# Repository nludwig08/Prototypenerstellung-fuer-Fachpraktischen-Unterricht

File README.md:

# Prototypenerstellung für den Fachpraktischen Unterricht

Fünf elektronische Projekte für Schnupperschüler an der HTL Steyr.

| Nr. | Projekt | Beschreibung |
|-----|---------|--------------|
| 01 | [Elektronischer Würfel](01-elektronischer-wuerfel/) | ... |
| 02 | [Hau den Lukas](02-hau-den-lukas/) | ... |
| 03 | [Merkspiel](03-merkspiel/) | ... |
| 04 | [Zeitrate-Spiel](04-zeitrate-spiel/) | ... |
| 05 | [Wecker](05-wecker/) | ... |

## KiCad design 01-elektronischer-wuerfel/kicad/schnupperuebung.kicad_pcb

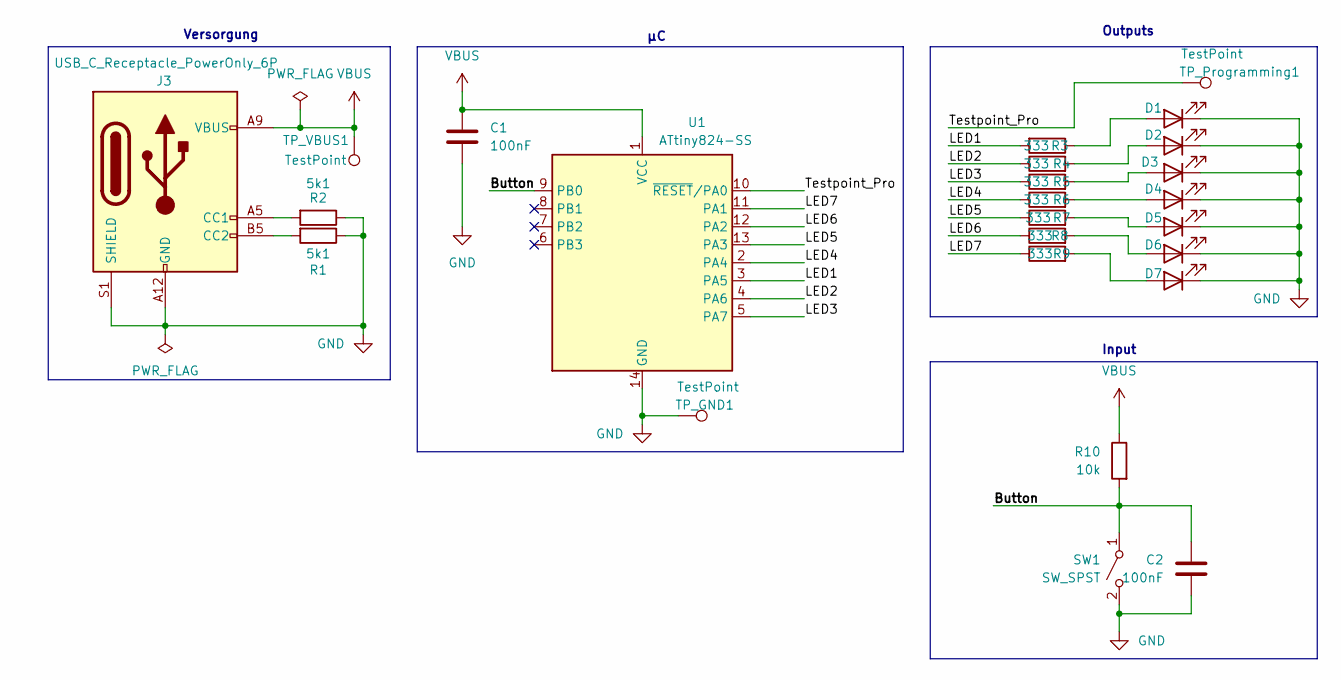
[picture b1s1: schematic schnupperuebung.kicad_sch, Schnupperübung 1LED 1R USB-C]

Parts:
C1, C2: 100nF; C_Disc_D5.0mm_W2.5mm_P5.00mm
D1, D2, D3, D4, D5, D6, D7: LED; LED_D5.0mm
J3: USB_C_Receptacle_PowerOnly_6P; USB_C_Receptacle_GCT_USB4125-xx-x-0190_6P_TopMnt_Horizontal
R1, R2: 5k1; R_0805_2012Metric_Pad1.20x1.40mm_HandSolder
R3, R4, R5, R6, R7, R8, R9: 333; R_Axial_DIN0207_L6.3mm_D2.5mm_P10.16mm_Horizontal
R10: 10k; R_Axial_DIN0207_L6.3mm_D2.5mm_P10.16mm_Horizontal
SW1: SW_SPST; C_Radial_D5.0mm_H5.0mm_P2.00mm
TP_GND1: TestPoint; TestPoint_Pad_D4.0mm
TP_Programming1: TestPoint; TestPoint_Pad_D4.0mm
TP_VBUS1: TestPoint; TestPoint_Pad_D4.0mm
U1: ATtiny824-SS; SOIC-14_3.9x8.7mm_P1.27mm

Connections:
/Button: C2.2, R10.2, SW1.1 (A), U1.9 (PB0)
/LED1: R3.2, U1.3 (PA5)
/LED2: R4.1, U1.4 (PA6)
/LED3: R5.1, U1.5 (PA7)
/LED4: R6.1, U1.2 (PA4)
/LED5: R7.1, U1.13 (PA3)
/LED6: R8.1, U1.12 (PA2)
/LED7: R9.1, U1.11 (PA1)
/Testpoint_Pro: TP_Programming1.1 (1_1), U1.10 (~RESET/PA0)
GND: C1.1, C2.1, D1.1 (K), D2.1 (K), D3.1 (K), D4.1 (K), D5.1 (K), D6.1 (K), D7.1 (K), J3.A12 (GND), J3.B12 (GND), J3.S1 (SHIELD), R1.1, R2.1, SW1.2 (B), TP_GND1.1 (1_1), U1.14 (GND)
unnamed: D1.2 (A), R3.1
unnamed: D2.2 (A), R4.2
unnamed: D3.2 (A), R5.2
unnamed: D4.2 (A), R6.2
unnamed: D5.2 (A), R7.2
unnamed: D6.2 (A), R8.2
unnamed: D7.2 (A), R9.2
unnamed: J3.A5 (CC1), R2.2
unnamed: J3.B5 (CC2), R1.2
VBUS: C1.2, J3.A9 (VBUS), J3.B9 (VBUS), R10.1, TP_VBUS1.1 (1_1), U1.1 (VCC)

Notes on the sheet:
Outputs
Input
Versorgung

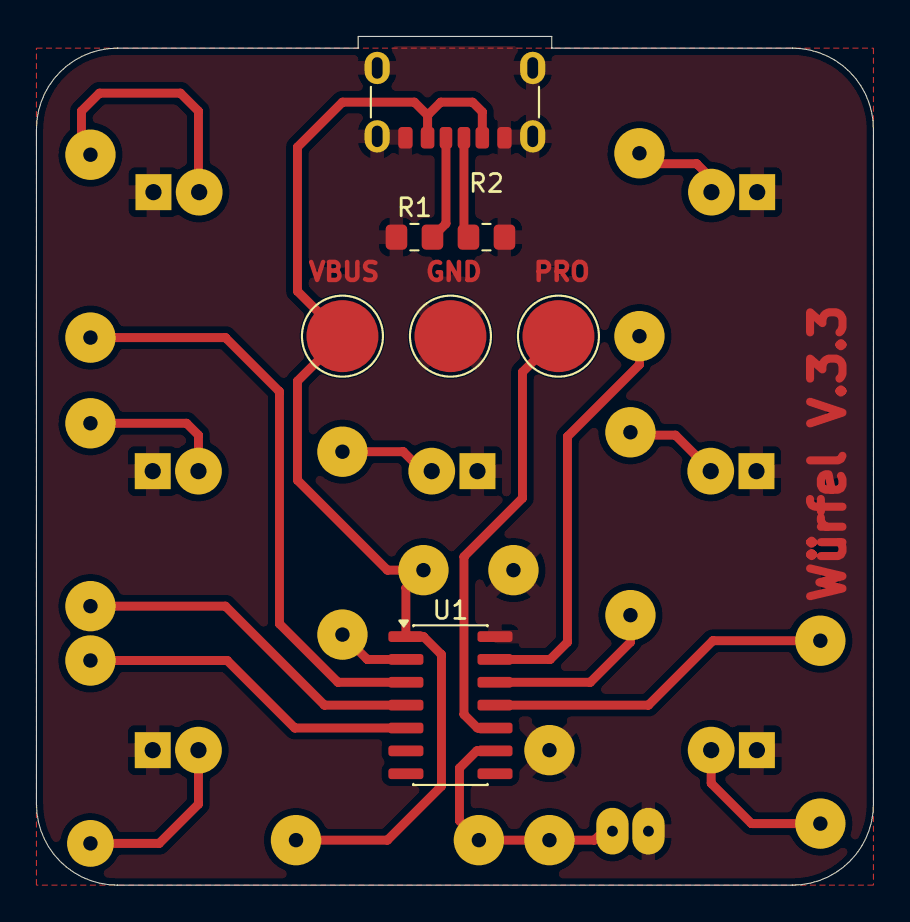
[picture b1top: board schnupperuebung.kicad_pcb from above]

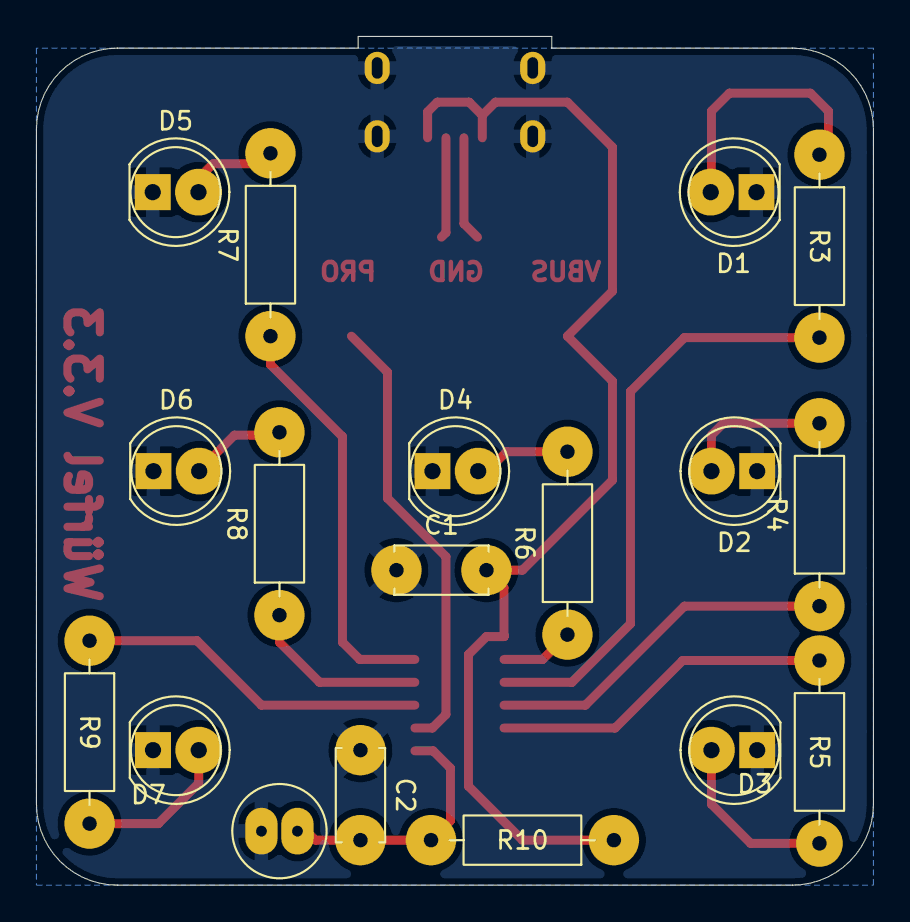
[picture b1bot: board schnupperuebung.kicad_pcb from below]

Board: 2 copper layers, 46.5 x 47.1 mm, 25 parts (18 on the bottom side), 20 nets.
